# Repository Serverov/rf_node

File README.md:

rf_node
=======

Wireless node for home automation (Arduino compatible)

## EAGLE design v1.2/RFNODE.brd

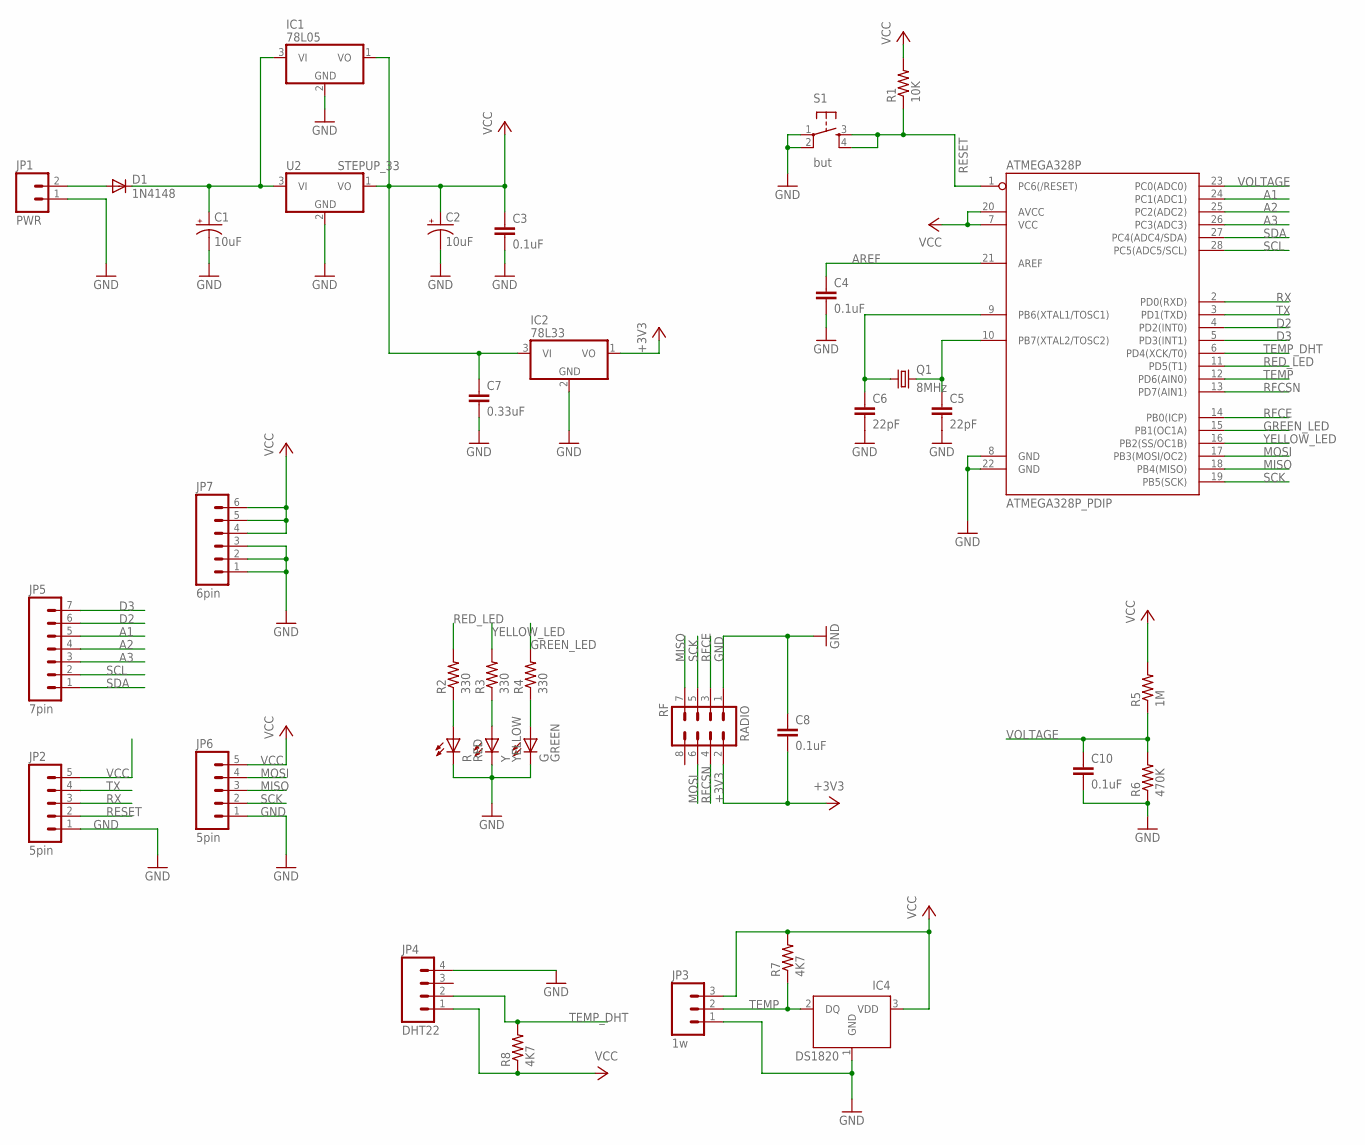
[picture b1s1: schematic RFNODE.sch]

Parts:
ATMEGA328P: ATMEGA328P_PDIP; DIL28-3
C1, C2: 10uF; E2-4
C3, C4, C8, C10: 0.1uF; C1206
C5, C6: 22pF; C1206
C7: 0.33uF; C1206
D1: 1N4148; D-2.5
G: GREEN; LED3MM
IC1: 78L05; TO92
IC2: 78L33; TO92
IC4: DS1820; TO-92
JP1: PWR; MOLEX-1X2
JP2, JP6: 5pin; 1X05
JP3: 1w; 1X03
JP4: DHT22; 1X04
JP5: 7pin; 1X07
JP7: 6pin; 1X06
Q1: 8MHz; HC49/S
R: RED; LED3MM
R1: 10K; R1206
R2, R3, R4: 330; R1206
R5: 1M; R1206
R6: 470K; R1206
R7, R8: 4K7; R1206
RADIO: RF; 2X4
S1: but; TACTILE-PTH
U2: STEPUP_33; 1X03
Y: YELLOW; LED3MM

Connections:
+3V3: C8.2, IC2.1 (VO), RADIO.2
A1: ATMEGA328P.24 (PC1(ADC1)), JP5.5
A2: ATMEGA328P.25 (PC2(ADC2)), JP5.4
A3: ATMEGA328P.26 (PC3(ADC3)), JP5.3
AREF: ATMEGA328P.21 (AREF), C4.1
D2: ATMEGA328P.4 (PD2(INT0)), JP5.6
D3: ATMEGA328P.5 (PD3(INT1)), JP5.7
GND: ATMEGA328P.8 (GND), ATMEGA328P.22 (GND), C1.-, C2.-, C3.2, C4.2, C5.2, C6.2, C7.2, C8.1, C10.2, G.K (C), IC1.2 (GND), IC2.2 (GND), IC4.1 (GND), JP1.1, JP2.1, JP3.1, JP4.4, JP6.1, JP7.1, JP7.2, JP7.3, R.K (C), R6.1, RADIO.1, S1.1, S1.2, U2.2 (GND), Y.K (C)
GREEN_LED: ATMEGA328P.15 (PB1(OC1A)), R4.2
MISO: ATMEGA328P.18 (PB4(MISO)), JP6.4, RADIO.7
MOSI: ATMEGA328P.17 (PB3(MOSI/OC2)), JP6.3, RADIO.6
unnamed: R.A, R2.1
unnamed: R3.1, Y.A
unnamed: G.A, R4.1
RAW: D1.A, JP1.2
RAW_PROT: C1.+, D1.C, IC1.3 (VI), U2.3 (VI)
RED_LED: ATMEGA328P.11 (PD5(T1)), R2.2
RESET: ATMEGA328P.1 (PC6(/RESET)), JP2.2, R1.1, S1.3, S1.4
RFCE: ATMEGA328P.14 (PB0(ICP)), RADIO.3
RFCSN: ATMEGA328P.13 (PD7(AIN1)), RADIO.4
RX: ATMEGA328P.2 (PD0(RXD)), JP2.3
SCK: ATMEGA328P.19 (PB5(SCK)), JP6.2, RADIO.5
SCL: ATMEGA328P.28 (PC5(ADC5/SCL)), JP5.1
SDA: ATMEGA328P.27 (PC4(ADC4/SDA)), JP5.2
TEMP: ATMEGA328P.12 (PD6(AIN0)), IC4.2 (DQ), JP3.2, R7.1
TEMP_DHT: ATMEGA328P.6 (PD4(XCK/T0)), JP4.2, R8.2
TX: ATMEGA328P.3 (PD1(TXD)), JP2.4
VCC: ATMEGA328P.7 (VCC), ATMEGA328P.20 (AVCC), C2.+, C3.1, C7.1, IC1.1 (VO), IC2.3 (VI), IC4.3 (VDD), JP2.5, JP3.3, JP4.1, JP6.5, JP7.4, JP7.5, JP7.6, R1.2, R5.2, R7.2, R8.1, U2.1 (VO)
VOLTAGE: ATMEGA328P.23 (PC0(ADC0)), C10.1, R5.1, R6.2
XTAL1: ATMEGA328P.9 (PB6(XTAL1/TOSC1)), C6.1, Q1.1
XTAL2: ATMEGA328P.10 (PB7(XTAL2/TOSC2)), C5.1, Q1.2
YELLOW_LED: ATMEGA328P.16 (PB2(SS/OC1B)), R3.2

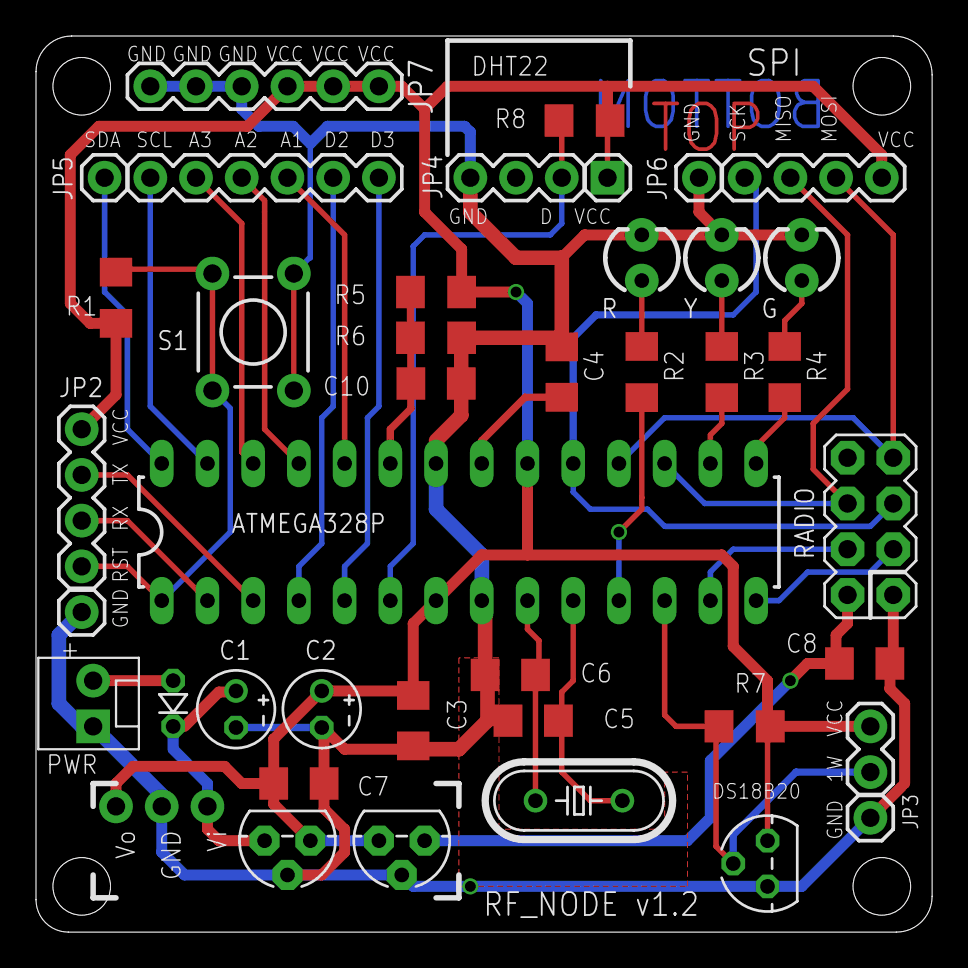
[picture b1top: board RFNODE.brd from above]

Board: 2 copper layers, 49.8 x 49.8 mm, 36 parts (0 on the bottom side), 32 nets.

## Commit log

2014-01-04 v1.2

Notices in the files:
parts and their libraries:
SparkFun-DigitalIC: Licensing: CC v3.0 Share-Alike You are welcome to use this library for commercial purposes.
